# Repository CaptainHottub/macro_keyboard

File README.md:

# macro_keyboard

13-Key USB Macro Keyboard using the [KB2040 Kee Boar Driver](https://www.adafruit.com/product/5302)

## Features

* The KB2040 MC communicates with the Python driver that runs on your computer
* **Wayland Support:** Optimized for Linux (Fedora/KDE) with Wayland support.
* 3x4 Grid with 12 keys and 1 mode button
* 2 Rotary encoders with buttons
* 15 Addressable RGB LED backlights.
* South Facing LED and sockets
* KAILH hot swap sockets

## Getting Started

macro_keyboard V2.4x was designed to use the [Adafruit KB2040 - RP2040 Kee Boar Driver](https://www.adafruit.com/product/5302).

> If you use a different micro controller, you will have to change the pins in the MC code.

The KB2040 currently runs [CircuitPython](https://circuitpython.org/) version 8.2.9 or newer.

#### Dependencies

**Linux (Fedora/KDE Wayland):**
The driver uses `qdbus` for native desktop switching on KDE Plasma.
If you require advanced window manipulation, we recommend installing `kdotool` (a drop-in replacement for `xdotool` on Wayland).

### KB2040 Setup

Follow Adafruit's guide to install CircuitPython: [https://learn.adafruit.com/adafruit-kb2040/circuitpython](https://learn.adafruit.com/adafruit-kb2040/circuitpython)

Install these libraries from the [**CircuitPython Library Bundle**](https://circuitpython.org/libraries):
* adafruit_hid
* adafruit_ticks.mpy
* neopixel.mpy

Move the `code.py` file found in `src/Microcontroller/` onto the KB2040.

### Python Driver Setup

The driver uses [Python 3.12](https://www.python.org/downloads/) or newer.

1. Clone the repo:
   ```bash
   git clone [https://github.com/CaptainHottub/macro_keyboard.git](https://github.com/CaptainHottub/macro_keyboard.git)
2.  Install Python dependencies:

    ```bash
    pip install -r requirements.txt
    ```

3.  **Configure the driver:**
    Edit `config.yml`. You can now use `~` to reference your home directory safely.

    ```yaml
    paths:
      sounds: "~/Documents/soundboard_audios" # Uses your home dir automatically
    ```

4.  Run the driver:

    ```bash
    python -u "src/Driver/driver_main.py"
    ```

-----

## User Macros (The Sandbox)

**New in v2.4:** You don't need to edit the complex driver code to add your own macros\!
Open `src/Driver/user_macros.py` and write your own Python code using the simple `@register` tool.

### How to add a macro:

1.  Open `user_macros.py`.
2.  Import the tools: `from macro_handlers import register, user_log, play_user_sound`.
3.  Write a function and decorate it.

**Example: Open VS Code**

```python
@register(button=5, app="Visual Studio Code")
def run_my_code():
    user_log("Running Code...")
    macros.perform_hotkey(['ctrl', 'alt', 'n'])
```

**Example: Play a Sound**

```python
@register(button=6, layers=('Mode',))
def victory_sound():
    play_user_sound("victory.mp3") # Plays from your configured sound folder
```

**Example: Encoder Knob**

```python
from macro_handlers import register_encoder

@register_encoder(encoder_id=1, action='RR') # Rotate Right
def volume_up():
    macros.SpotifyController().event_handler('VolumeUp')
```

-----

### Assembling the PCB

The production Gerber zip file is in `src/PCB/Macro_PCB_2.2.x_Production_Gerber`.
The Bill Of Material is at `/src/macro_keyboard_BOM.csv`.

**Bottom Mount Components**

  * 13 KAILH Hot Swap Sockets
  * 12 Diodes (Pay attention to orientation\!)
  * 15 SK6812-E RGB LEDS
  * 330 OHM Resistor

    > **Pay close attention to the position of the diode and especially the LED**

**Top Mount Components**

  * KB2040
  * 6x6mm Tactile Switch
  * 2x Rotary Encoders

### 3D Printed Case

The `Case/` folder contains STLs for the case.

  * **Top Case:** Acts as the plate for key switches.

  * **Bottom Case:** Two versions available (with and without reset hole).

    > **Left: `Bottom_Case_with_hole_V2.stl`    
    Right: `Bottom_Case_No_Hole_V2.stl`**

  * Uses 4 M3x12mm or M3x10mm screws.

    The top half also serves as a plate that the keys snap into.

## Inspiration

Inspired by Ryan Bates and his [Macro Keyboard Video](https://www.youtube.com/watch?v=IDlcxLQ1SbY).

## License, Copyright, and Legal
All software and hardware designs in this repository are licensed under the [Creative Commons Attribution-NonCommercial 4.0 International][cc-by-nc] license.

[![CC BY-NC 4.0][cc-by-nc-image]][cc-by-nc]

[cc-by-nc]: https://creativecommons.org/licenses/by-nc/4.0/
[cc-by-nc-image]: https://licensebuttons.net/l/by-nc/4.0/88x31.png

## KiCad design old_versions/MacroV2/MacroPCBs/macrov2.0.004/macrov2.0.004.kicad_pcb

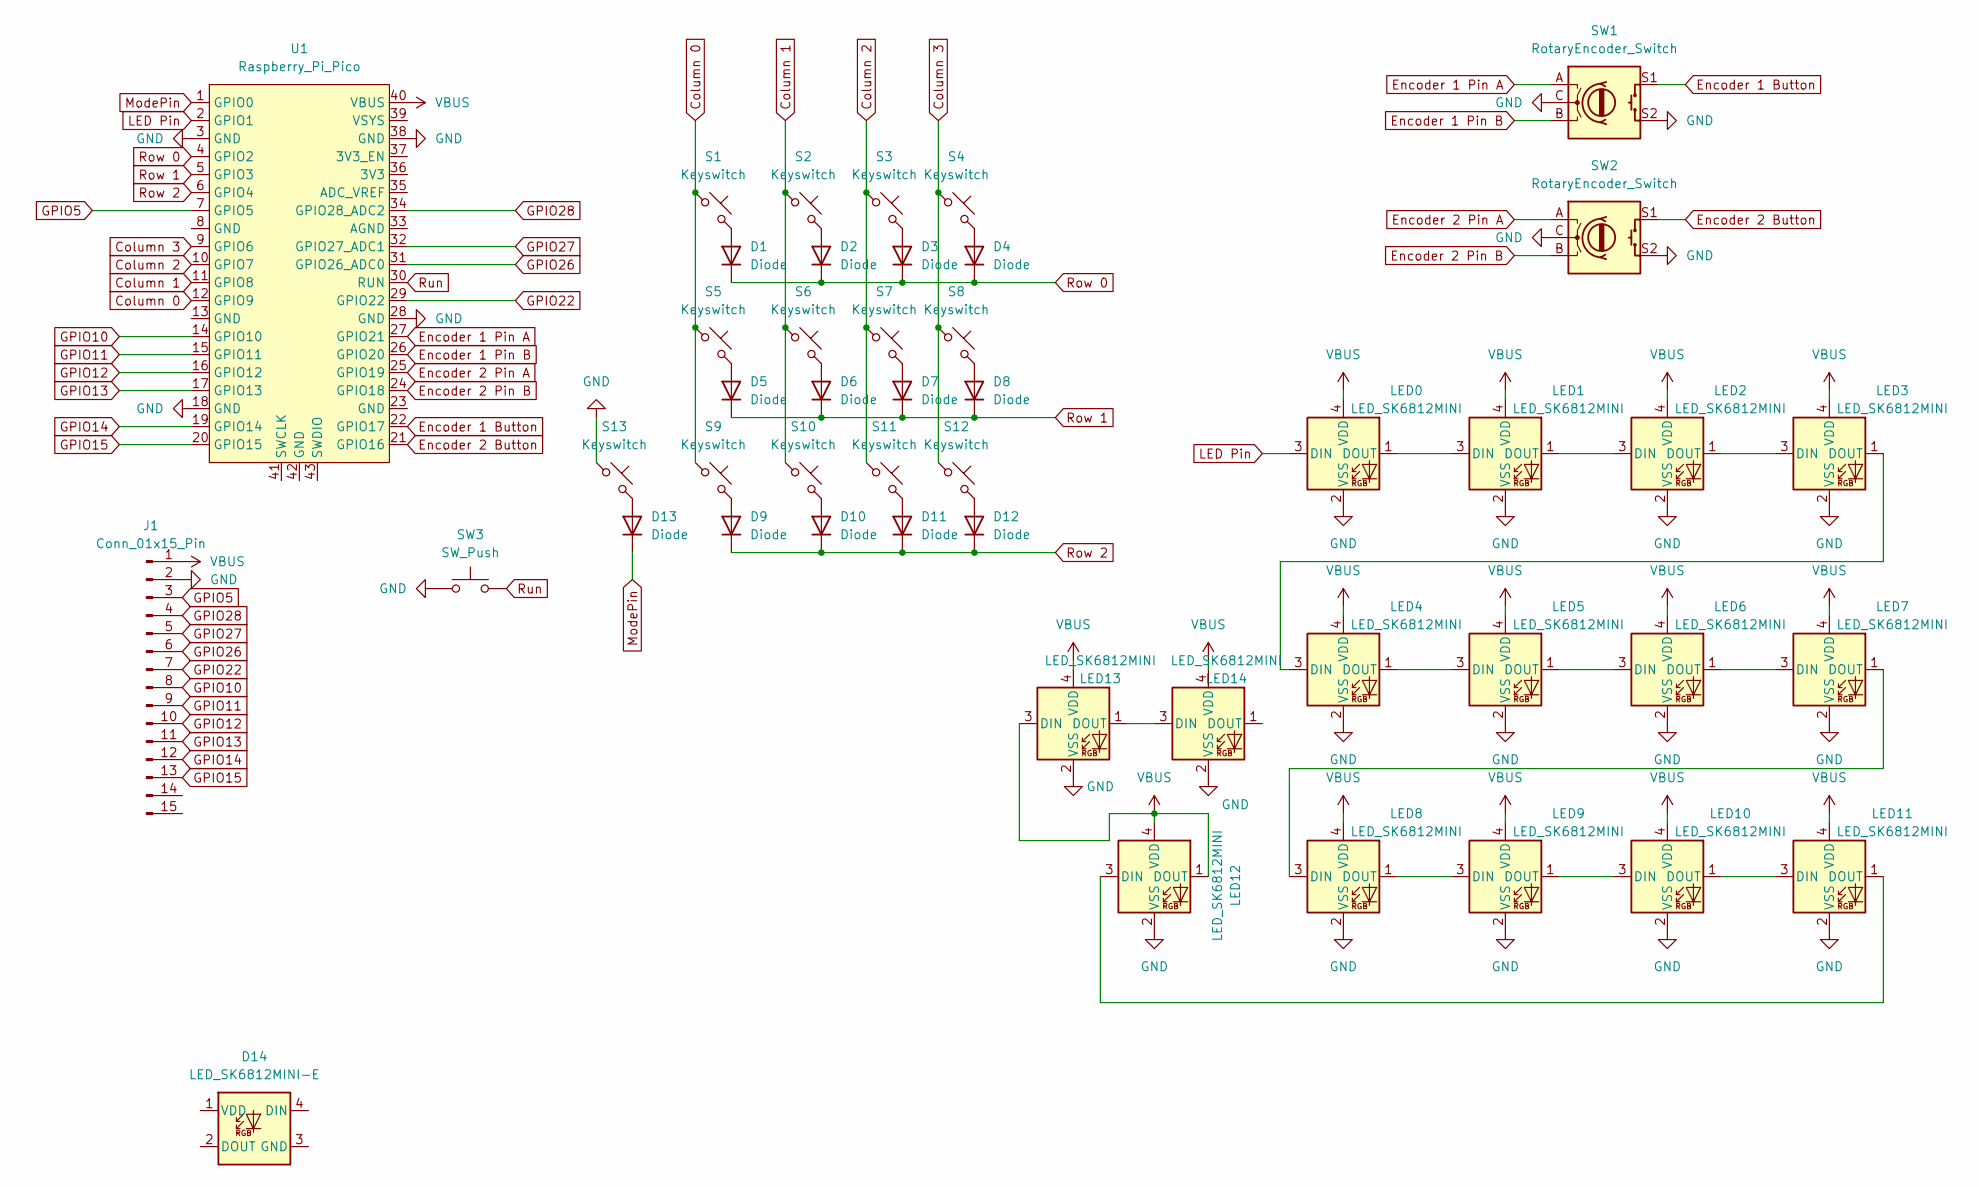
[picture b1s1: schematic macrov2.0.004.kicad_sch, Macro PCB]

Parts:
D1, D2, D3, D4, D5, D6, D7, D8, D9, D10, D11, D12, D13: Diode; Diode_SOD-123
D14: LED_SK6812MINI-E
J1: Conn_01x15_Pin; PinHeader_1x15_P2.54mm_Vertical
LED0, LED1, LED2, LED3, LED4, LED5, LED6, LED7, LED8, LED9, LED10, LED11, LED12, LED13, LED14: LED_SK6812MINI
S1, S2, S3, S4, S5, S6, S7, S8, S9, S10, S11, S12, S13: Keyswitch; Hotswap_MX_Plated_1.00u
SW1, SW2: RotaryEncoder_Switch; RotaryEncoder_Alps_EC11E-Switch_Vertical_H20mm
SW3: SW_Push; SW_PUSH_6mm_H7.3mm
U1: Raspberry_Pi_Pico

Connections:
Column 0: S1.1, S5.1, S9.1, U1.12 (GPIO9)
Column 1: S2.1, S6.1, S10.1, U1.11 (GPIO8)
Column 2: S3.1, S7.1, S11.1, U1.10 (GPIO7)
Column 3: S4.1, S8.1, S12.1, U1.9 (GPIO6)
Encoder 1 Button: SW1.S1, U1.22 (GPIO17)
Encoder 1 Pin A: SW1.A, U1.27 (GPIO21)
Encoder 1 Pin B: SW1.B, U1.26 (GPIO20)
Encoder 2 Button: SW2.S1, U1.21 (GPIO16)
Encoder 2 Pin A: SW2.A, U1.25 (GPIO19)
Encoder 2 Pin B: SW2.B, U1.24 (GPIO18)
GND: J1.2, LED0.2 (VSS), LED1.2 (VSS), LED2.2 (VSS), LED3.2 (VSS), LED4.2 (VSS), LED5.2 (VSS), LED6.2 (VSS), LED7.2 (VSS), LED8.2 (VSS), LED9.2 (VSS), LED10.2 (VSS), LED11.2 (VSS), LED12.2 (VSS), LED13.2 (VSS), LED14.2 (VSS), S13.1, SW1.C, SW1.S2, SW2.C, SW2.S2, SW3.1, U1.3 (GND), U1.18 (GND), U1.28 (GND), U1.38 (GND)
GPIO5: J1.3, U1.7 (GPIO5)
GPIO10: J1.8, U1.14 (GPIO10)
GPIO11: J1.9, U1.15 (GPIO11)
GPIO12: J1.10, U1.16 (GPIO12)
GPIO13: J1.11, U1.17 (GPIO13)
GPIO14: J1.12, U1.19 (GPIO14)
GPIO15: J1.13, U1.20 (GPIO15)
GPIO22: J1.7, U1.29 (GPIO22)
GPIO26: J1.6, U1.31 (GPIO26_ADC0)
GPIO27: J1.5, U1.32 (GPIO27_ADC1)
GPIO28: J1.4, U1.34 (GPIO28_ADC2)
LED Pin: LED0.3 (DIN), U1.2 (GPIO1)
ModePin: D13.1 (K), U1.1 (GPIO0)
unnamed: D1.2 (A), S1.2
unnamed: D2.2 (A), S2.2
unnamed: D3.2 (A), S3.2
unnamed: D4.2 (A), S4.2
unnamed: D5.2 (A), S5.2
unnamed: D6.2 (A), S6.2
unnamed: D7.2 (A), S7.2
unnamed: D8.2 (A), S8.2
unnamed: D9.2 (A), S9.2
unnamed: D10.2 (A), S10.2
unnamed: D11.2 (A), S11.2
unnamed: D12.2 (A), S12.2
unnamed: D13.2 (A), S13.2
unnamed: LED0.1 (DOUT), LED1.3 (DIN)
unnamed: LED1.1 (DOUT), LED2.3 (DIN)
unnamed: LED2.1 (DOUT), LED3.3 (DIN)
unnamed: LED3.1 (DOUT), LED4.3 (DIN)
unnamed: LED4.1 (DOUT), LED5.3 (DIN)
unnamed: LED5.1 (DOUT), LED6.3 (DIN)
unnamed: LED6.1 (DOUT), LED7.3 (DIN)
unnamed: LED7.1 (DOUT), LED8.3 (DIN)
unnamed: LED8.1 (DOUT), LED9.3 (DIN)
unnamed: LED9.1 (DOUT), LED10.3 (DIN)
unnamed: LED10.1 (DOUT), LED11.3 (DIN)
unnamed: LED11.1 (DOUT), LED12.3 (DIN)
unnamed: LED13.1 (DOUT), LED14.3 (DIN)
Row 0: D1.1 (K), D2.1 (K), D3.1 (K), D4.1 (K), U1.4 (GPIO2)
Row 1: D5.1 (K), D6.1 (K), D7.1 (K), D8.1 (K), U1.5 (GPIO3)
Row 2: D9.1 (K), D10.1 (K), D11.1 (K), D12.1 (K), U1.6 (GPIO4)
Run: SW3.2, U1.30 (RUN)
VBUS: J1.1, LED0.4 (VDD), LED1.4 (VDD), LED2.4 (VDD), LED3.4 (VDD), LED4.4 (VDD), LED5.4 (VDD), LED6.4 (VDD), LED7.4 (VDD), LED8.4 (VDD), LED9.4 (VDD), LED10.4 (VDD), LED11.4 (VDD), LED12.1 (DOUT), LED12.4 (VDD), LED13.3 (DIN), LED13.4 (VDD), LED14.4 (VDD), U1.40 (VBUS)

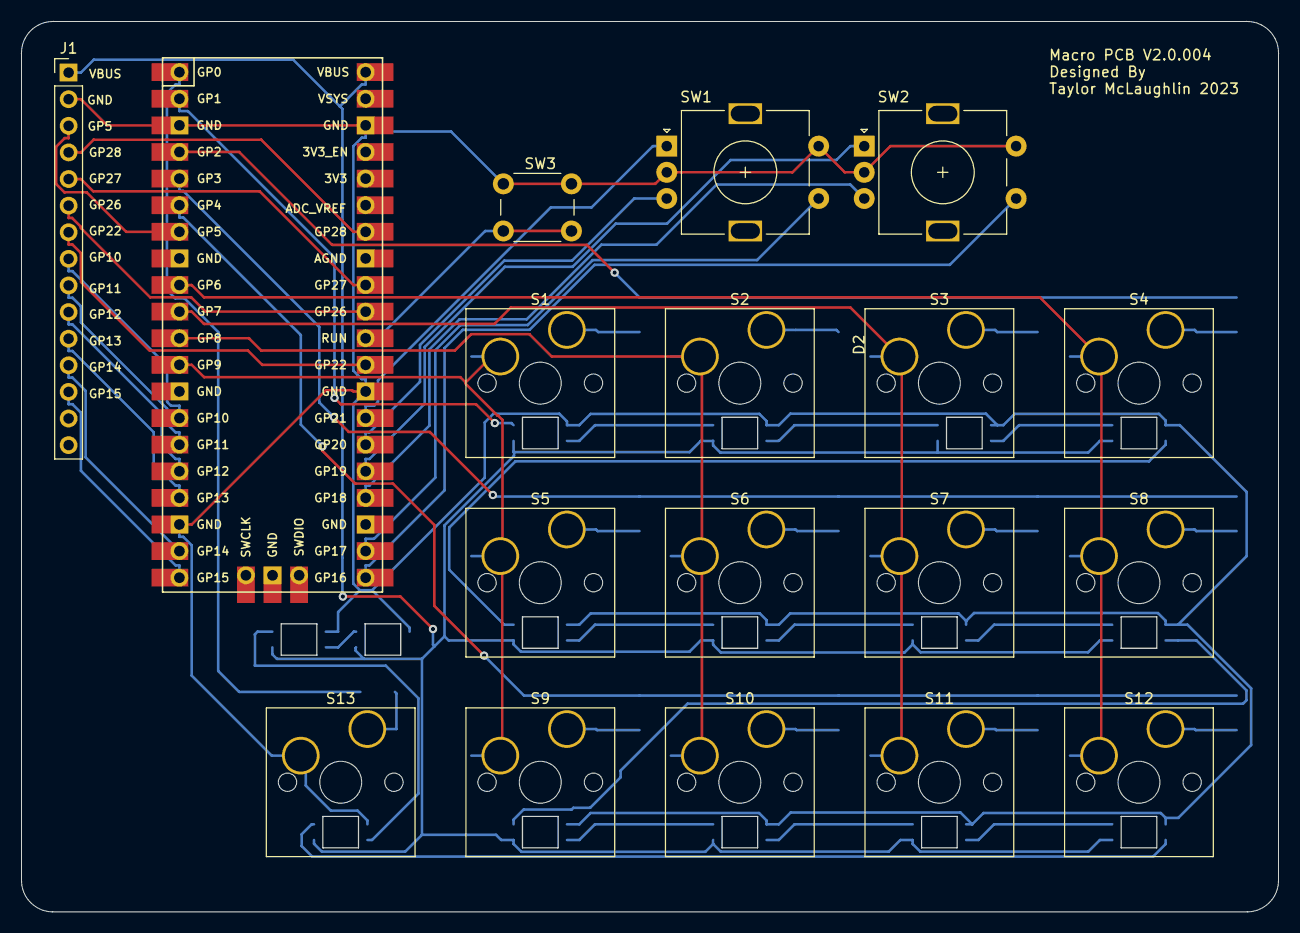
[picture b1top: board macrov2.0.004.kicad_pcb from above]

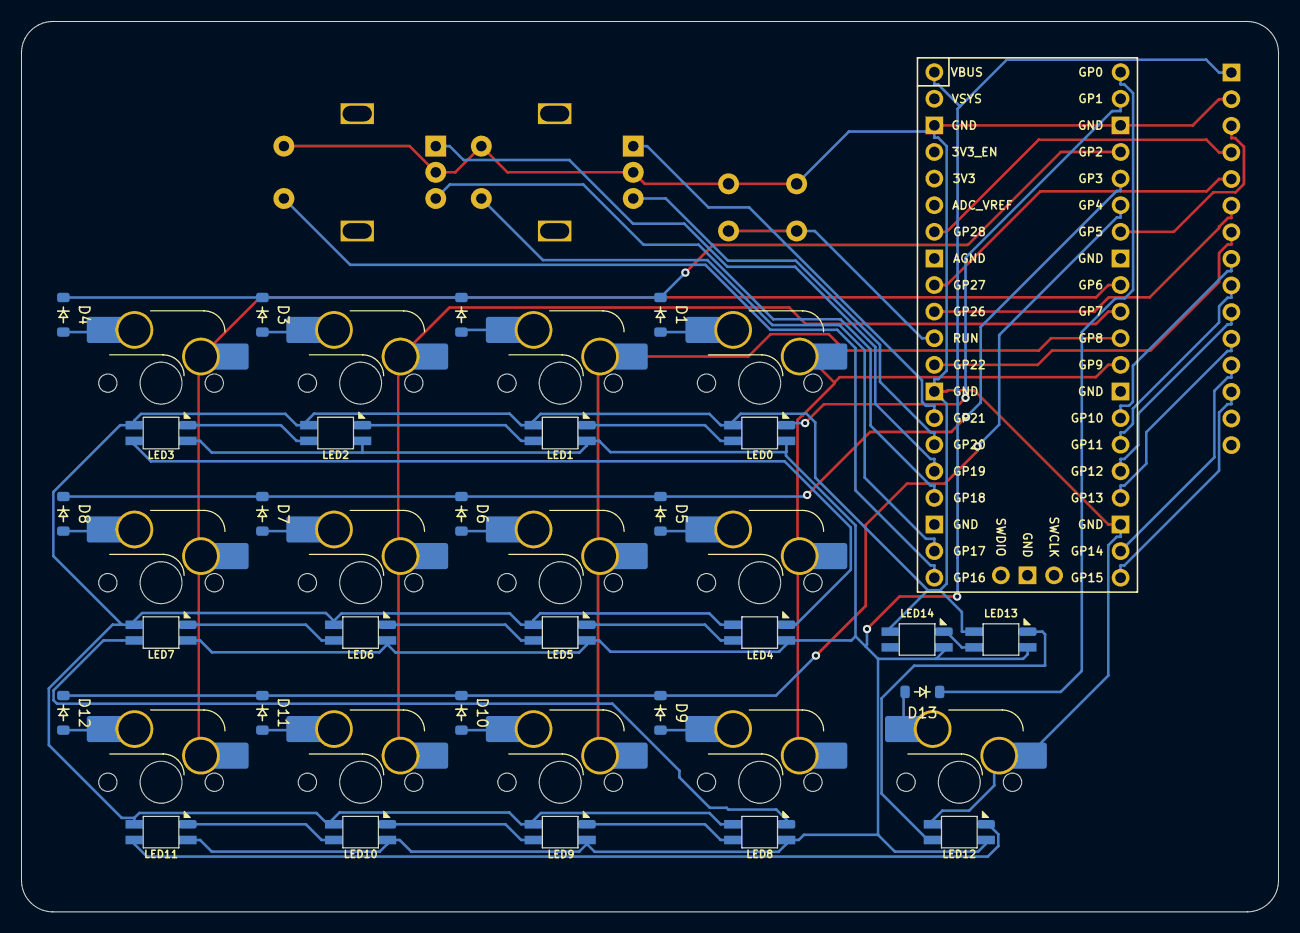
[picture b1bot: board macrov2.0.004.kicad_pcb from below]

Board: 2 copper layers, 120.0 x 85.0 mm, 46 parts (13 on the bottom side), 55 nets.

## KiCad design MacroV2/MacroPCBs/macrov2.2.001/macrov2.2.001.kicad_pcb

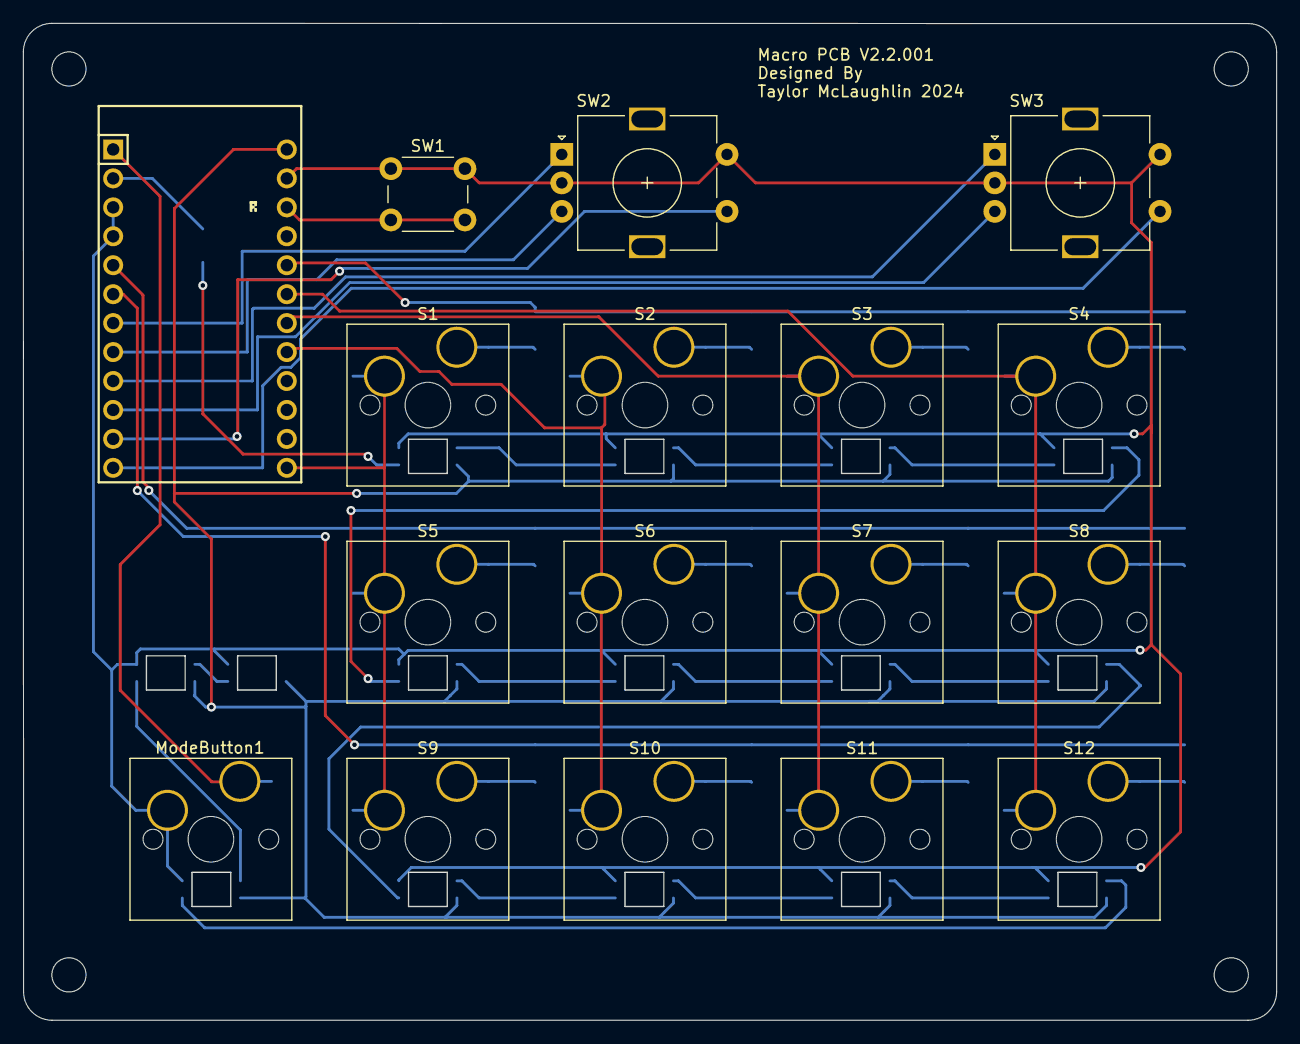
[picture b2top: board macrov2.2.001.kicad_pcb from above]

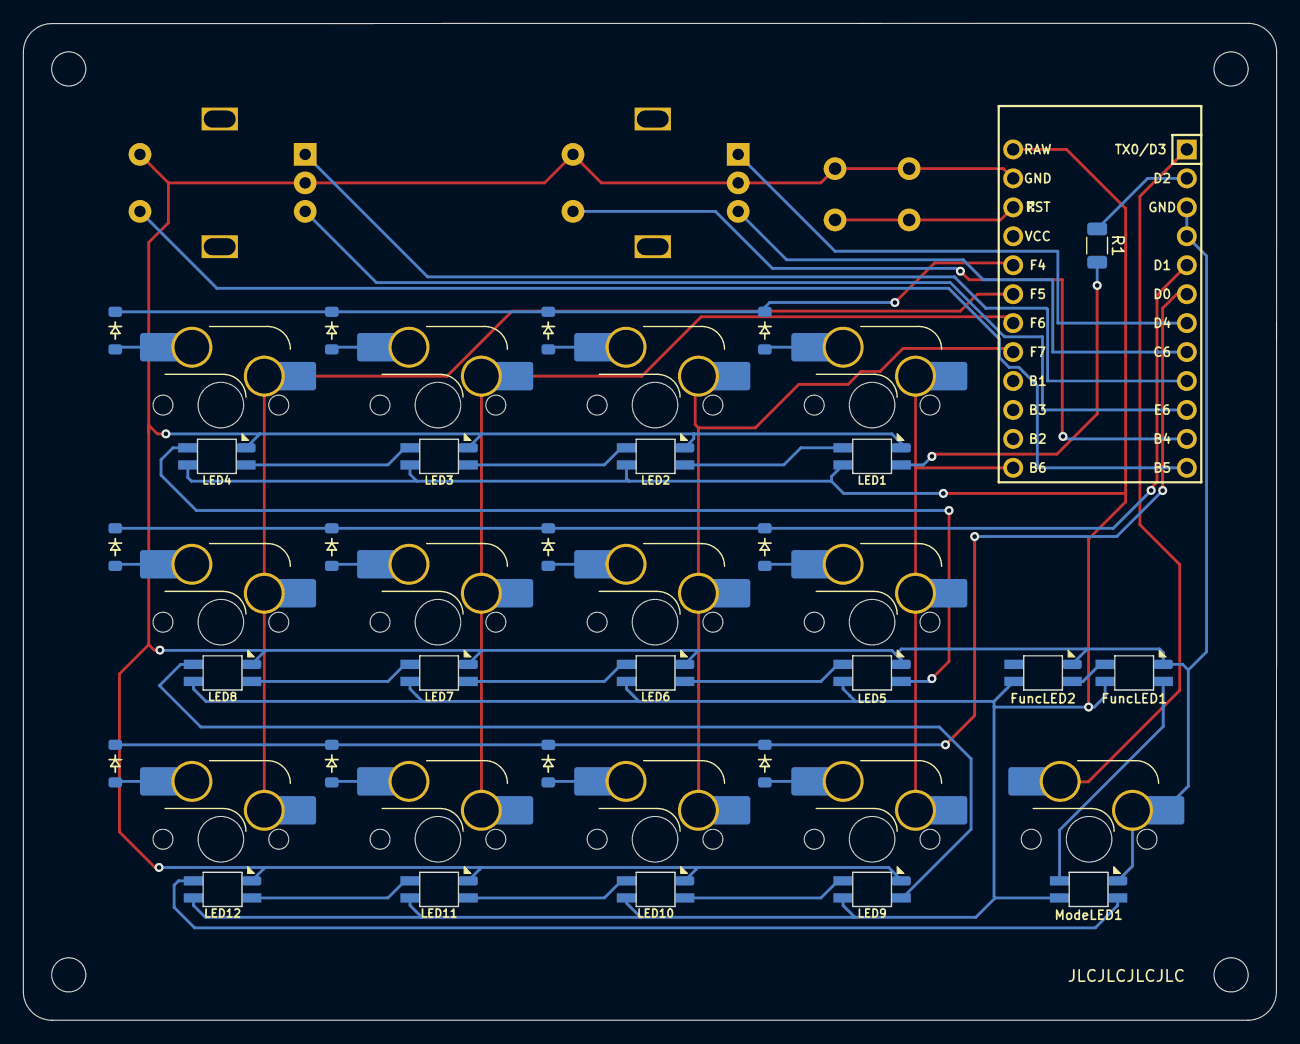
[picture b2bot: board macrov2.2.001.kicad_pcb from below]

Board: 2 copper layers, 110.0 x 87.5 mm, 45 parts (28 on the bottom side), 45 nets.

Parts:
D1, D2, D3, D4, D5, D6, D7, D8, D9, D10, D11, D12: Diode; Diode_SOD-123
FuncLED1, FuncLED2: LED_SK6812MINI-E
LED1, LED2, LED3, LED4, LED5, LED6, LED7, LED8, LED9, LED10, LED11, LED12: LED_SK6812MINI-E
ModeButton1: Keyswitch; Hotswap_MX_Plated_1.00u
ModeLED1: LED_SK6812MINI-E
R1: Resistor; R_1206_3216Metric
S1, S2, S3, S4, S5, S6, S7, S8, S9, S10, S11, S12: Keyswitch; Hotswap_MX_Plated_1.00u
SW1: SW_Push; SW_PUSH_6mm_H7.3mm
SW2, SW3: RotaryEncoder_Switch; RotaryEncoder_Alps_EC11E-Switch_Vertical_H20mm
U2: Arduino_Pro_Micro

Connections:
Column 0: S1.1, S5.1, S9.1, U2.13 (10/PB6)
Column 1: S2.1, S6.1, S10.1, U2.17 (A0/PF7)
Column 2: S3.1, S7.1, S11.1, U2.18 (A1/PF6)
Column 3: S4.1, S8.1, S12.1, U2.19 (A2/PF5)
Encoder 1 Button: SW2.S1, U2.11 (8/PB4)
Encoder 1 Pin A: SW2.A, U2.7 (4/PD4)
Encoder 1 Pin B: SW2.B, U2.8 (5/PC6)
Encoder 2 Button: SW3.S1, U2.12 (9/PB5)
Encoder 2 Pin A: SW3.A, U2.9 (6/PD7)
Encoder 2 Pin B: SW3.B, U2.10 (7/PE6)
GND: FuncLED1.3 (GND), FuncLED2.3 (GND), LED1.3 (GND), LED2.3 (GND), LED3.3 (GND), LED4.3 (GND), LED5.3 (GND), LED6.3 (GND), LED7.3 (GND), LED8.3 (GND), LED9.3 (GND), LED10.3 (GND), LED11.3 (GND), LED12.3 (GND), ModeButton1.1, ModeLED1.3 (GND), SW1.1, SW2.C, SW2.S2, SW3.C, SW3.S2, U2.3 (GND), U2.4 (GND), U2.23 (GND)
LED Pin: R1.1, U2.2 (RX1/PD2)
ModePin: ModeButton1.2, U2.1 (TX0/PD3)
unnamed: D1.2 (A), S1.2
unnamed: D2.2 (A), S2.2
unnamed: D3.2 (A), S3.2
unnamed: D4.2 (A), S4.2
unnamed: D5.2 (A), S5.2
unnamed: D6.2 (A), S6.2
unnamed: D7.2 (A), S7.2
unnamed: D8.2 (A), S8.2
unnamed: D9.2 (A), S9.2
unnamed: D10.2 (A), S10.2
unnamed: D11.2 (A), S11.2
unnamed: D12.2 (A), S12.2
unnamed: FuncLED1.4 (DIN), ModeLED1.2 (DOUT)
unnamed: FuncLED1.2 (DOUT), FuncLED2.4 (DIN)
unnamed: LED1.4 (DIN), R1.2
unnamed: LED1.2 (DOUT), LED2.4 (DIN)
unnamed: LED2.2 (DOUT), LED3.4 (DIN)
unnamed: LED3.2 (DOUT), LED4.4 (DIN)
unnamed: LED4.2 (DOUT), LED5.4 (DIN)
unnamed: LED5.2 (DOUT), LED6.4 (DIN)
unnamed: LED6.2 (DOUT), LED7.4 (DIN)
unnamed: LED7.2 (DOUT), LED8.4 (DIN)
unnamed: LED8.2 (DOUT), LED9.4 (DIN)
unnamed: LED9.2 (DOUT), LED10.4 (DIN)
unnamed: LED10.2 (DOUT), LED11.4 (DIN)
unnamed: LED11.2 (DOUT), LED12.4 (DIN)
unnamed: LED12.2 (DOUT), ModeLED1.4 (DIN)
RST: SW1.2, U2.22 (RST)
Row 0: D1.1 (K), D2.1 (K), D3.1 (K), D4.1 (K), U2.20 (A3/PF4)
Row 1: D5.1 (K), D6.1 (K), D7.1 (K), D8.1 (K), U2.5 (2/PD1)
Row 2: D9.1 (K), D10.1 (K), D11.1 (K), D12.1 (K), U2.6 (3/PD0)
VBUS: FuncLED1.1 (VDD), FuncLED2.1 (VDD), LED1.1 (VDD), LED2.1 (VDD), LED3.1 (VDD), LED4.1 (VDD), LED5.1 (VDD), LED6.1 (VDD), LED7.1 (VDD), LED8.1 (VDD), LED9.1 (VDD), LED10.1 (VDD), LED11.1 (VDD), LED12.1 (VDD), ModeLED1.1 (VDD), U2.24 (RAW)

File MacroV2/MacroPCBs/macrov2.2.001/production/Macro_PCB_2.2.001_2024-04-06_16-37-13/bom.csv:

Designator,Footprint,Quantity,Value,LCSC Part #
"D1, D10, D11, D12, D2, D3, D4, D5, D6, D7, D8, D9",Diode_SOD-123,12,Diode,
"FuncLED1, FuncLED2, LED1, LED10, LED11, LED12, LED2, LED3, LED4, LED5, LED6, LED7, LED8, LED9, ModeLED1",LED_SK6812MINI-E,15,LED_SK6812MINI-E,
"ModeButton1, S1, S10, S11, S12, S2, S3, S4, S5, S6, S7, S8, S9",Hotswap_MX_Plated_1.00u,13,Keyswitch,
R1,1206,1,Resistor,
SW1,SW_PUSH_6mm_H7.3mm,1,SW_Push,
"SW2, SW3",RotaryEncoder_Alps_EC11E-Switch_Vertical_H20mm,2,RotaryEncoder_Switch,
U2,Arduino_Pro_Micro,1,Arduino_Pro_Micro,

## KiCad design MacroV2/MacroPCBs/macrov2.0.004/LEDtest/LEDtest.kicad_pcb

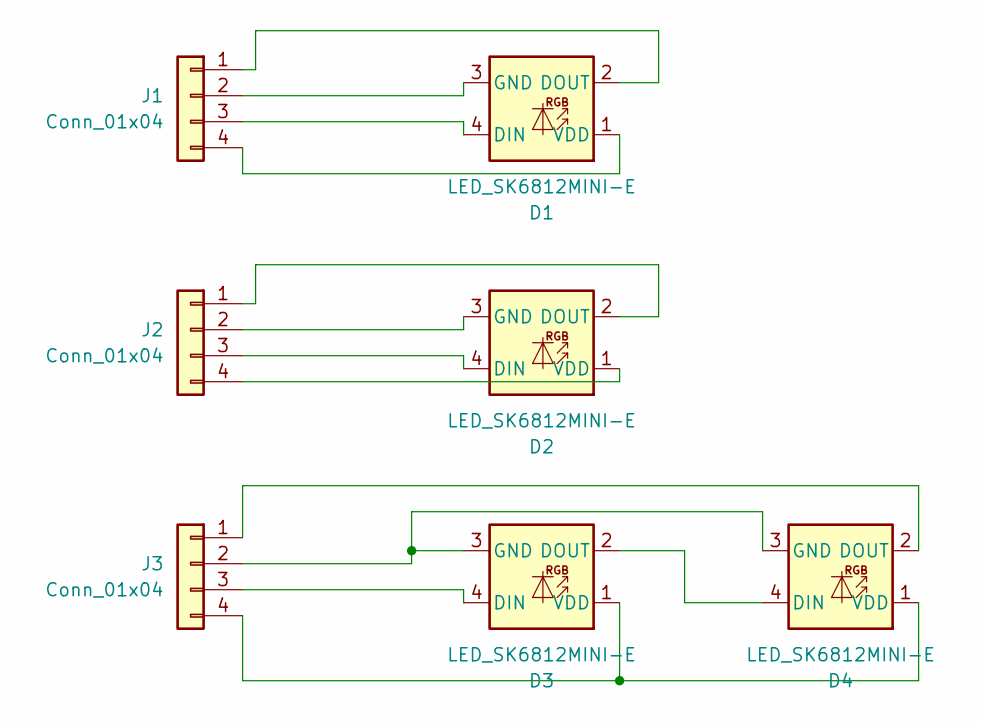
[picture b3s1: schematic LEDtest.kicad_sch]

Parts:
D1, D2, D3, D4: LED_SK6812MINI-E
J1, J2, J3: Conn_01x04; PinHeader_1x04_P2.54mm_Vertical

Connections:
unnamed: D1.4 (DIN), J1.3
unnamed: D1.2 (DOUT), J1.1
unnamed: D1.3 (GND), J1.2
unnamed: D1.1 (VDD), J1.4
unnamed: D2.4 (DIN), J2.3
unnamed: D2.2 (DOUT), J2.1
unnamed: D2.3 (GND), J2.2
unnamed: D2.1 (VDD), J2.4
unnamed: D3.4 (DIN), J3.3
unnamed: D3.2 (DOUT), D4.4 (DIN)
unnamed: D3.3 (GND), D4.3 (GND), J3.2
unnamed: D3.1 (VDD), D4.1 (VDD), J3.4
unnamed: D4.2 (DOUT), J3.1

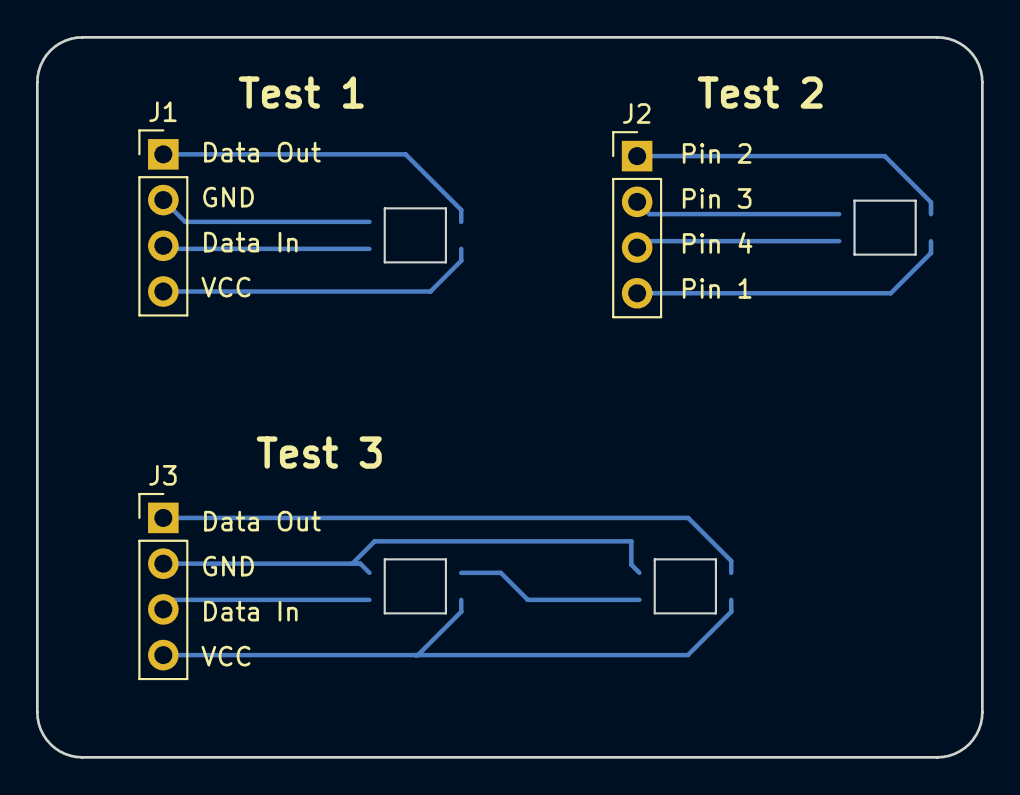
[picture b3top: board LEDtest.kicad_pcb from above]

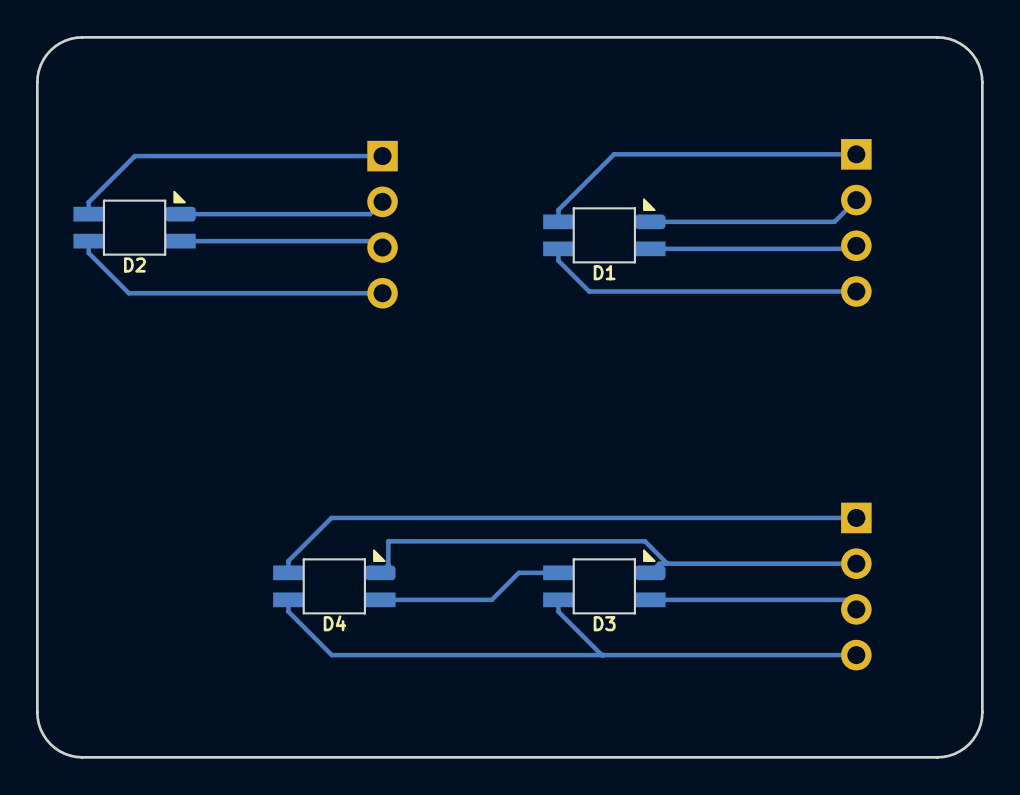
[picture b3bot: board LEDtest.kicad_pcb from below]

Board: 2 copper layers, 52.5 x 40.0 mm, 7 parts (4 on the bottom side), 13 nets.

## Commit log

2022-05-19 init
2022-05-19 Master
2022-05-22 Idea for image to text
2022-05-23 Fixed a bug
2022-05-24 edit
2022-05-24 testing custom keyboard inputs
2022-05-25 testing
2022-05-25 update to macroV2_2
2022-05-26 first implementation of custom_keyboard
2022-05-26 Slight changes
2022-05-26 add to TODO
2022-05-26 custom_keyboard now has 1 dictionary of keycodes
2022-05-30 added shiftright so it doesnt lock movement
2022-09-19 Just added Delays for the star Citizen macros
2022-09-22 Just making things look better
2022-09-22 New version and new Icon, see Macro_changes.txt to see what changed
2022-09-22 Added Notifications
2022-09-22 New version of setup
2022-09-22 New versionn of setup
2022-10-21 Nothing changed
2022-10-27 just a test
2022-10-29 spotify should work faster and better now.
2022-10-29 updated changes
2022-10-29 just testing
2022-12-06 Bug Fixes and QOL improvements
2022-12-06 Trying To commit
2022-12-06 Just changed the pythonIcon
2022-12-13 Bug fixing
2022-12-13 Runs Task Manager when button 8 is pressed
2022-12-13 Was testing something
2023-01-27 Added new macros and removed unnecessary stuff
2023-01-31 Added tts functinality
2023-02-01 Changed spotify func timeout
2023-03-01 I Dont remember what I did
2023-03-01 Removed TTS and fixed a bug in spotifyV2
2023-03-01 Minor thing
2023-03-02 Fixed Text To Speech and added a stop Speech
2023-03-02 Fixed bug with tts
2023-03-03 New Version, I merged Macro and funcs
2023-03-03 Just logs
2023-03-03 Changed Where Logs go
2023-03-07 commented out stuff
2023-03-07 minor fix, added func timer but is commented out
2023-03-07 Updated TODO
2023-03-07 minor fix
2023-03-10 Fixed an issue with spotifyV2 and added to TODO
2023-03-10 Ideas to improve tts in code
2023-03-10 Made spotify func smaller and added new features
2023-03-10 Writing idea for new image to text in test
2023-03-14 Updated the text formating in textToSpeech
2023-03-14 I don't need to format text for textToSpeech
2023-03-14 Updated image to text, it now opens snippet mode
2023-03-14 added a func that checks and creates a log folder
2023-03-15 Added a new macro, it is a test, it uses autoit
2023-03-16 Updated to version 3.1
2023-03-16 Added toaster definition to logger
2023-03-17 edited rocket_flying() and added wellskate()
2023-03-24 Worked on wellskate and rocketflying
2023-03-24 Minor things
2023-04-11 Added arduino code. CODE WILL NOT WORK
2023-04-11 Arduino Code testing
2023-04-12 Working on Arduino code
2023-04-12 Created a 3.2, Has not been tested yet
2023-04-27 Added a new macro.
2023-06-07 Update readme.md
    Added information about play pause, next and previous song macro
2023-07-08 Updated Button Mode text
2023-07-08 Added arduino code to V3.2
2023-07-15 Added a pause feature in V3.1.2
2023-07-15 Updated Pythonicon
2023-10-20 Removed the Async part from textToSpeech
2023-10-20 Was just testing something
2023-12-15 Started Using a new Microcontroller
2023-12-15 Update readme.md
    Preparing to update to a new version
2023-12-20 test
2023-12-20 Repository Structure Update
2023-12-20 Updated Readme and Todos
2023-12-21 PCB revisions, Newest is in production
2024-01-09 Update readme.md
    PCB assembled and mistakes made when designing it.
2024-01-09 Working on microcontroller code
2024-01-16 Updated Microcontroller code
2024-03-29 It works now
2024-04-02 Macro Driver now works like Prev Version.
2024-04-02 Hmmm?
2024-04-02 TTS Note
2024-04-02 DevLog and readme changes
2024-04-02 Readme update
2024-04-02 Updated Icon
2024-04-02 Driver Will now connect to macro
2024-04-02 Fixed Chrome Audio Controller Actions dict
2024-04-02 Playing with spotifyControlTest
2024-04-02 Updated Readme'S
2024-04-02 Changed click time in Image_to_text2
2024-04-02 Added Zoom in and Zoom out funcs to encoder2
2024-04-02 OnboardLEd now turns on for encoders
2024-04-03 New Macro MoveSpotifyToCurrentDesktop()
2024-04-03 New Macro now works
2024-04-05 Updated to python 3.12.2
2024-04-06 Removed code from Image_to_text2(), the onboard LED on Microcontroller now works
2024-04-06 New PCB Revision
2024-04-16 v2.2.801 is a test, 2.2.001 is still the main one.
2024-04-16 Rewrote the parser
2024-04-16 Uppdated ReadMe
2024-04-16 fixed parser
2024-04-17 Added Images
2024-04-17 Added Image to readme
2024-04-17 added image of PCB to README
2024-04-17 Added a License
2024-04-17 LICENSE FIX
2024-04-19 New Minor Version, v2.2.101
2024-04-19 Repo Structure Change
2024-04-19 gitignore changes
2024-04-19 gitignore update
2024-04-19 gitignoretest
2024-04-19 rwas
2024-04-20 Changed Spotify Controls
2024-04-20 ReadMe updates
2024-04-20 Added Case 3D model
2024-04-20 zoomin and zoomout macro for LibreOffice Draw
2024-04-20 Added a zoomin and zoomout macro for LibreOffice Draw
2024-04-22 chromeAudioControl is more reliable
2024-06-07 Minor changes
2024-06-07 Removed unessisary comments
2024-06-08 First commit to this branch
2024-06-08 First commit to this branch2
2024-06-08 little bit of testing
2024-06-08 I hope this works on windows
2024-06-08 I hope thi works 2x
2024-06-08 This works on Windows
2024-06-08 Works on Linux and Windows
2024-06-08 Changelog and TODO update
2024-06-10 It should be easier to test macros now
2024-06-10 Some more logging
2024-06-11 Linux compatibility testing
2024-06-13 Some macros work on linux
2024-06-13 Will a file be ignored?
2024-06-13 it didnt
2024-06-28 I belive most of the macros will work on linux.
2024-06-28 TODO update
2024-06-29 Requirements file, FireFox media controller and TTS works
2024-07-05 Semi-update
2024-07-15 You can send Data over serial to the microcontroller
2024-10-31 Small Updates
2024-11-01 new Images and small Tweaks
2024-11-01 Updated Images Names
2024-11-01 Fixed image name
2024-11-01 New README
2024-11-01 MediaController now use Mpris2 package
2024-11-01 platform specific packages in requirements.txt
2024-11-01 Github actions update
2024-11-01 Github actions update again
2024-11-01 Github actions update again again
2024-11-01 Github actions update again again cubed
2024-11-02 little test for github actions
2024-11-02 Github actions update again again 4x
2024-11-02 New Logging level and implemented Spotify.move_spotify_window()
2025-09-18 Added Soundboard funtionality, Temporary fix for recursion limit crash, temp disabled any window info func
2025-09-18 Things I forgot
2025-11-26 Update to requirements.txt and _windows_macro for windows compatibility
2025-12-07 missed this
2025-12-07 version 2.4.001, major changed to codebase.
2026-01-14 2.4.002 Minor changes, Button Led show when its a layer.
2026-01-23 Temp fix for microcontroller name change between windows and linux
2026-04-01 New Experimental Feature, Never Tested ON windows
2026-04-01 Removed 3.11 and added 3.14 to workflow, Plus update to it.
2026-04-01 Commented out PyCairo from requirements.txt
2026-04-01 Attempting to fix the sys icon on linux
